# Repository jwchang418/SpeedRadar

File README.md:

# SpeedRadar

This project is designed by Jun-Wei Chang for a simple speed radar by using a few of electronic components.

<br/>

Components list  
[here](https://github.com/jwchang418/SpeedRadar/blob/master/Components%20List.pdf)<br/>

<br/>
<br/>
<br/>
<br/>
Enjoy it !!

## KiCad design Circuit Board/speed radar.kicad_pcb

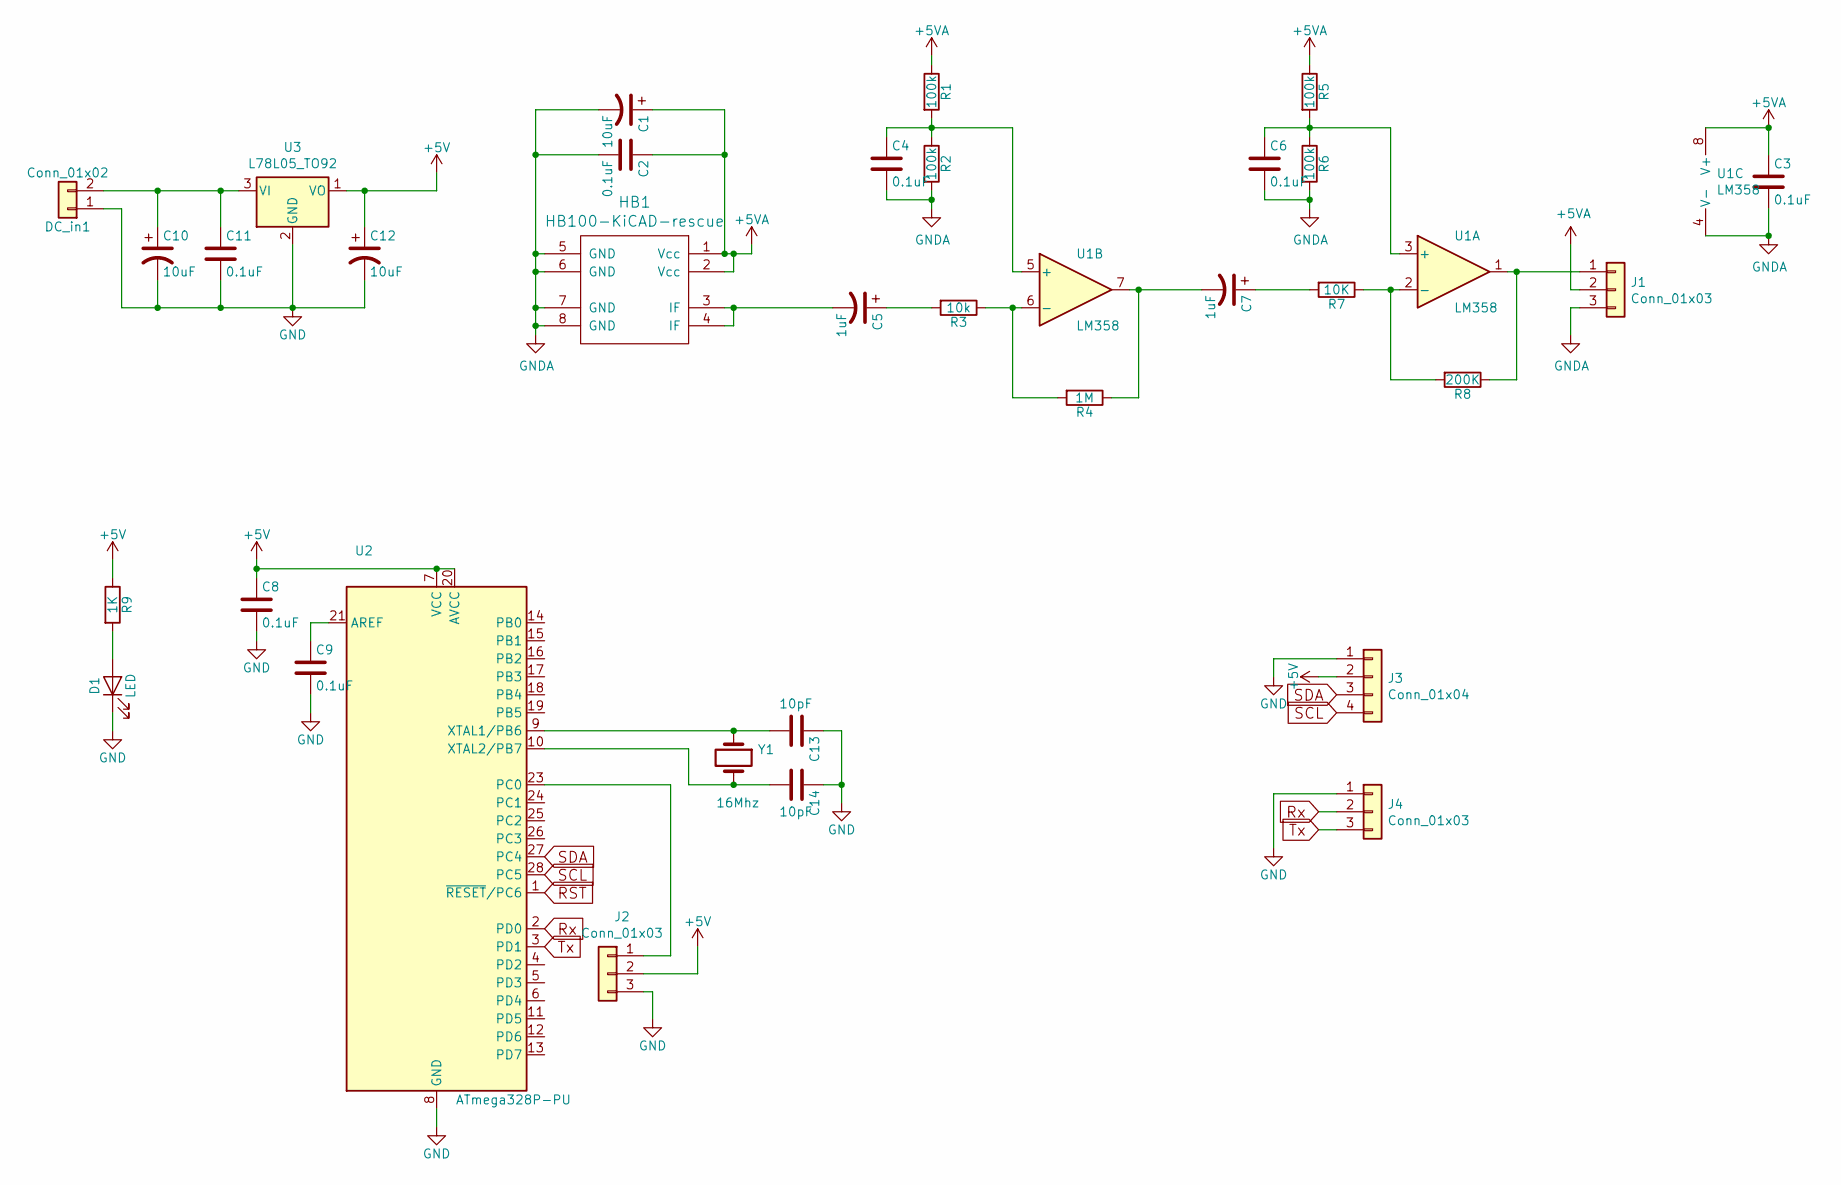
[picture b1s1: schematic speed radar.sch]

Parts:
C1, C10, C12: 10uF; CP_Radial_D4.0mm_P2.00mm
C2, C3, C4, C6, C8, C9, C11: 0.1uF; C_Disc_D3.0mm_W1.6mm_P2.50mm
C5, C7: 1uF; CP_Radial_D4.0mm_P2.00mm
C13, C14: 10pF; C_Disc_D3.0mm_W1.6mm_P2.50mm
D1: LED; LED_D3.0mm
DC_in1: Conn_01x02; Molex_KK-254_AE-6410-02A_1x02_P2.54mm_Vertical
HB1: HB100-KiCAD-rescue; HB100_ver2
J1, J2: Conn_01x03; PinHeader_1x03_P2.54mm_Vertical
J3: Conn_01x04; PinHeader_1x04_P2.54mm_Vertical
J4: Conn_01x03; Molex_KK-254_AE-6410-03A_1x03_P2.54mm_Vertical
R1, R2, R5, R6: 100k; R_Axial_DIN0207_L6.3mm_D2.5mm_P10.16mm_Horizontal
R3: 10k; R_Axial_DIN0207_L6.3mm_D2.5mm_P10.16mm_Horizontal
R4: 1M; R_Axial_DIN0207_L6.3mm_D2.5mm_P10.16mm_Horizontal
R7: 10K; R_Axial_DIN0207_L6.3mm_D2.5mm_P10.16mm_Horizontal
R8: 200K; R_Axial_DIN0207_L6.3mm_D2.5mm_P10.16mm_Horizontal
R9: 1K; R_Axial_DIN0207_L6.3mm_D2.5mm_P10.16mm_Horizontal
U1: LM358
U2: ATmega328P-PU; DIP-28_W7.62mm
U3: L78L05_TO92; TO-92_Inline_Wide
Y1: 16Mhz; Crystal_HC49-4H_Vertical

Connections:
+5V: C8.1, C12.1, J2.2, J3.2, R9.1, U2.7 (VCC), U2.20 (AVCC), U3.1 (VO)
+5VA: C1.1, C2.1, C3.1, HB1.1 (Vcc), HB1.2 (Vcc), J1.2, R1.1, R5.1, U1.8 (V+)
GND: C8.2, C9.2, C10.2, C11.2, C12.2, C13.1, C14.1, D1.1 (K), DC_in1.1, J2.3, J3.1, J4.1, U2.8 (GND), U2.22 (GND), U3.2 (GND)
GNDA: C1.2, C2.2, C3.2, C4.2, C6.2, HB1.5 (GND), HB1.6 (GND), HB1.7 (GND), HB1.8 (GND), J1.3, R2.2, R6.2, U1.4 (V-)
unnamed: C4.1, R1.2, R2.1, U1.5 (+)
unnamed: C5.1, R3.2
unnamed: C5.2, HB1.3 (IF), HB1.4 (IF)
unnamed: C6.1, R5.2, R6.1, U1.3 (+)
unnamed: C7.1, R7.2
unnamed: C7.2, R4.1, U1.7
unnamed: C9.1, U2.21 (AREF)
unnamed: C10.1, C11.1, DC_in1.2, U3.3 (VI)
unnamed: C13.2, U2.9 (XTAL1/PB6), Y1.1
unnamed: C14.2, U2.10 (XTAL2/PB7), Y1.2
unnamed: D1.2 (A), R9.2
unnamed: J1.1, R8.1, U1.1
unnamed: J2.1, U2.23 (PC0)
unnamed: R3.1, R4.2, U1.6 (-)
unnamed: R7.1, R8.2, U1.2 (-)
RST: U2.1 (~RESET~/PC6)
Rx: J4.2, U2.2 (PD0)
SCL: J3.4, U2.28 (PC5)
SDA: J3.3, U2.27 (PC4)
Tx: J4.3, U2.3 (PD1)

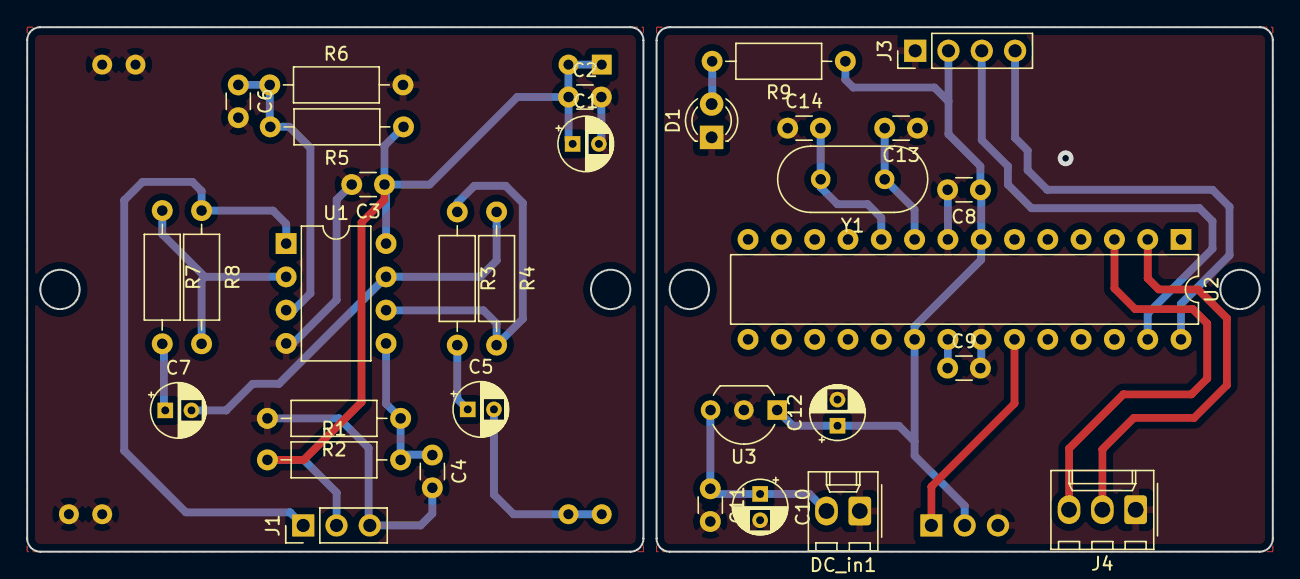
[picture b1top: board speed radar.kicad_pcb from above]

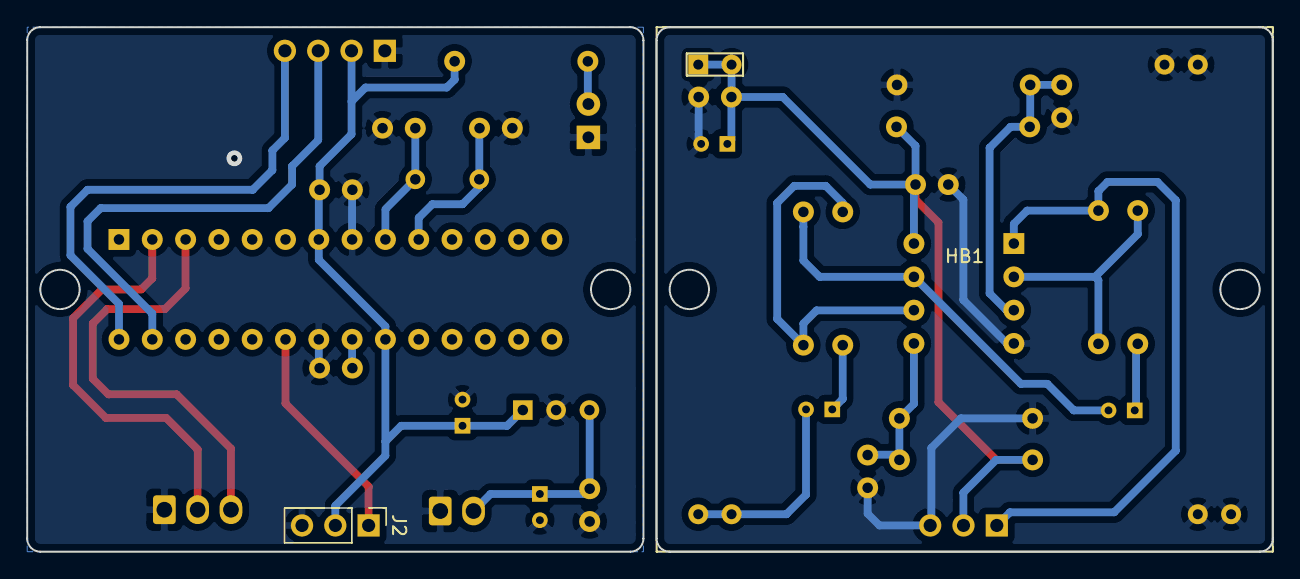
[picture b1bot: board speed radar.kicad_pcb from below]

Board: 2 copper layers, 95.0 x 40.0 mm, 34 parts (2 on the bottom side), 23 nets.

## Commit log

2020-06-08 Rename speed radar-cache.lib to KiCadFile/speed radar-cache.lib
2020-06-08 Rename speed radar-rescue.lib to KiCadFile/speed radar-rescue.lib
2020-06-08 Rename speed radar.kicad_pcb to KiCadFile/speed radar.kicad_pcb
2020-06-08 Rename speed radar.sch to KiCadFile/speed radar.sch
2020-06-08 Rename speed radar.pro to KiCadFile/speed radar.pro
2020-06-08 Rename Program.ino to Program/Program.ino
2020-06-08 Rename KiCadFile/speed radar-cache.lib to Circuit Board/speed radar-cache.lib
2020-06-08 Rename KiCadFile/speed radar-rescue.lib to Circuit Board/speed radar-rescue.lib
2020-06-08 Rename KiCadFile/speed radar.kicad_pcb to Circuit Board/speed radar.kicad_pcb
2020-06-08 Rename KiCadFile/speed radar.pro to Circuit Board/speed radar.pro
2020-06-08 Rename KiCadFile/speed radar.sch to Circuit Board/speed radar.sch
